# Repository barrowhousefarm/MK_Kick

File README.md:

# MK_Kick
Mortiz Klien Kick Drum

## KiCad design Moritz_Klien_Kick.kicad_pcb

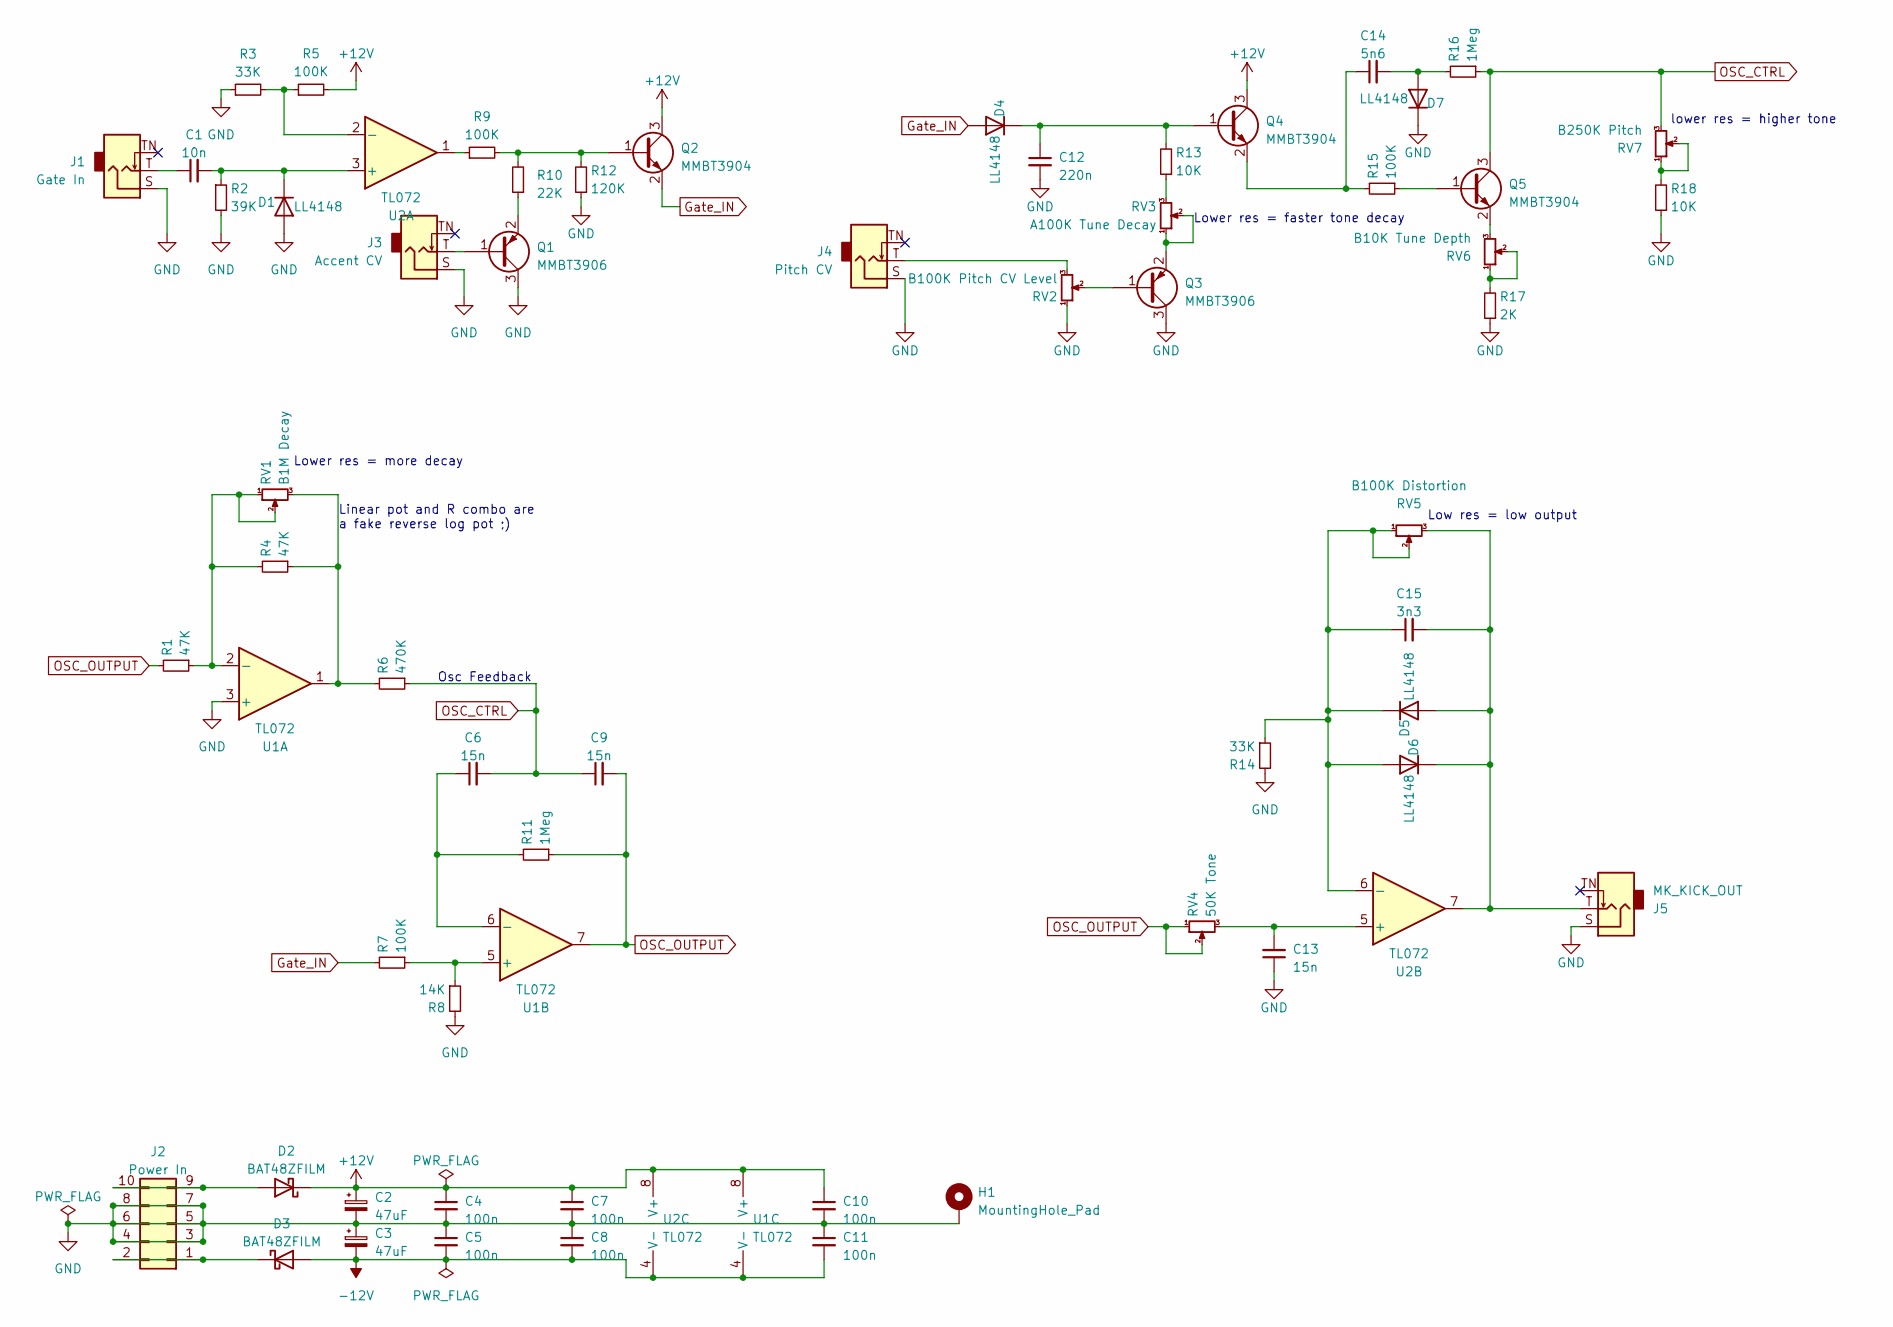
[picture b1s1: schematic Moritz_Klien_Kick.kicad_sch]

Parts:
C1: 10n; C_1210_3225Metric
C2, C3: 47uF; CP_Radial_D5.0mm_P2.50mm
C4, C5, C7, C8, C10, C11: 100n; C_1206_3216Metric
C6, C9, C13: 15n; C_1206_3216Metric
C12: 220n; C_1206_3216Metric
C14: 5n6; C_1206_3216Metric
C15: 3n3; C_1206_3216Metric
D1, D4, D5, D6, D7: LL4148; D_MiniMELF
D2, D3: BAT48ZFILM; D_MiniMELF
H1: MountingHole_Pad; MountingHole_3.2mm_M3_ISO14580_Pad
J1: Gate In; Jack_3.5mm_QingPu_WQP-PJ398SM_Vertical_CircularHoles
J2: Power In; IDC-Header_2x05_P2.54mm_Vertical
J3: Accent CV; Jack_3.5mm_QingPu_WQP-PJ398SM_Vertical_CircularHoles
J4: Pitch CV; Jack_3.5mm_QingPu_WQP-PJ398SM_Vertical_CircularHoles
J5: MK_KICK_OUT; Jack_3.5mm_QingPu_WQP-PJ398SM_Vertical_CircularHoles
Q1, Q3: MMBT3906; SOT-23
Q2, Q4, Q5: MMBT3904; SOT-23
R1, R4: 47K; R_1206_3216Metric
R2: 39K; R_1206_3216Metric
R3, R14: 33K; R_1206_3216Metric
R5, R7, R9, R15: 100K; R_1206_3216Metric
R6: 470K; R_1206_3216Metric
R8: 14K; R_1206_3216Metric
R10: 22K; R_1206_3216Metric
R11, R16: 1Meg; R_1206_3216Metric
R12: 120K; R_1206_3216Metric
R13, R18: 10K; R_1206_3216Metric
R17: 2K; R_1206_3216Metric
RV1: B1M Decay; Potentiometer_Alps_RK09K_Single_Vertical
RV2: B100K Pitch CV Level; Potentiometer_Alps_RK09K_Single_Vertical
RV3: A100K Tune Decay; Potentiometer_Alps_RK09K_Single_Vertical
RV4: 50K Tone; Potentiometer_Alps_RK09K_Single_Vertical
RV5: B100K Distortion; Potentiometer_Alps_RK09K_Single_Vertical
RV6: B10K Tune Depth; Potentiometer_Alps_RK09K_Single_Vertical
RV7: B250K Pitch; Potentiometer_Alps_RK09K_Single_Vertical
U1, U2: TL072; SO-8_5.3x6.2mm_P1.27mm

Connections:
+12V: C2.1, C4.1, C7.1, C10.1, D2.1 (K), Q2.3 (C), Q4.3 (C), R5.2, U1.8 (V+), U2.8 (V+)
-12V: C3.2, C5.2, C8.2, C11.2, D3.2 (A), U1.4 (V-), U2.4 (V-)
GND: C2.2, C3.1, C4.2, C5.1, C7.2, C8.1, C10.2, C11.1, C12.2, C13.1, D1.2 (A), D7.1 (K), H1.1, J1.S, J2.3, J2.4, J2.5, J2.6, J2.7, J2.8, J3.S, J4.S, J5.S, Q1.3 (C), Q3.3 (C), R2.2, R3.1, R8.2, R12.1, R14.2, R17.1, R18.1, RV2.1, U1.3 (+)
Gate_IN: D4.2 (A), Q2.2 (E), R7.2
unnamed: C1.1, J1.T
unnamed: C1.2, D1.1 (K), R2.1, U2.3 (+)
unnamed: D2.2 (A), J2.9, J2.10
unnamed: D3.1 (K), J2.1, J2.2
unnamed: C12.1, D4.1 (K), Q4.1 (B), R13.2
unnamed: C15.2, D5.2 (A), D6.1 (K), J5.T, RV5.3, U2.7
unnamed: C15.1, D5.1 (K), D6.2 (A), R14.1, RV5.1, RV5.2, U2.6 (-)
unnamed: C14.2, D7.2 (A), R16.2
unnamed: J4.T, RV2.3
unnamed: J3.T, Q1.1 (B)
unnamed: Q1.2 (E), R10.1
unnamed: Q2.1 (B), R9.2, R10.2, R12.2
unnamed: Q3.1 (B), RV2.2
unnamed: Q3.2 (E), RV3.1, RV3.2
unnamed: C14.1, Q4.2 (E), R15.2
unnamed: Q5.1 (B), R15.1
unnamed: Q5.2 (E), RV6.3
unnamed: R4.1, R6.2, RV1.3, U1.1
unnamed: R9.1, U2.1
unnamed: R13.1, RV3.3
unnamed: R17.2, RV6.1, RV6.2
unnamed: R18.2, RV7.1, RV7.2
unnamed: R1.1, R4.2, RV1.1, RV1.2, U1.2 (-)
unnamed: R7.1, R8.1, U1.5 (+)
unnamed: C6.1, R11.2, U1.6 (-)
unnamed: R3.2, R5.1, U2.2 (-)
unnamed: C13.2, RV4.3, U2.5 (+)
OSC_CTRL: C6.2, C9.1, Q5.3 (C), R6.1, R16.1, RV7.3
OSC_OUTPUT: C9.2, R1.2, R11.1, RV4.1, RV4.2, U1.7

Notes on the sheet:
Linear pot and R combo are a fake reverse log pot ;)
Low res = low output
Lower res = more decay
lower res = higher tone
Osc Feedback
Lower res = faster tone decay

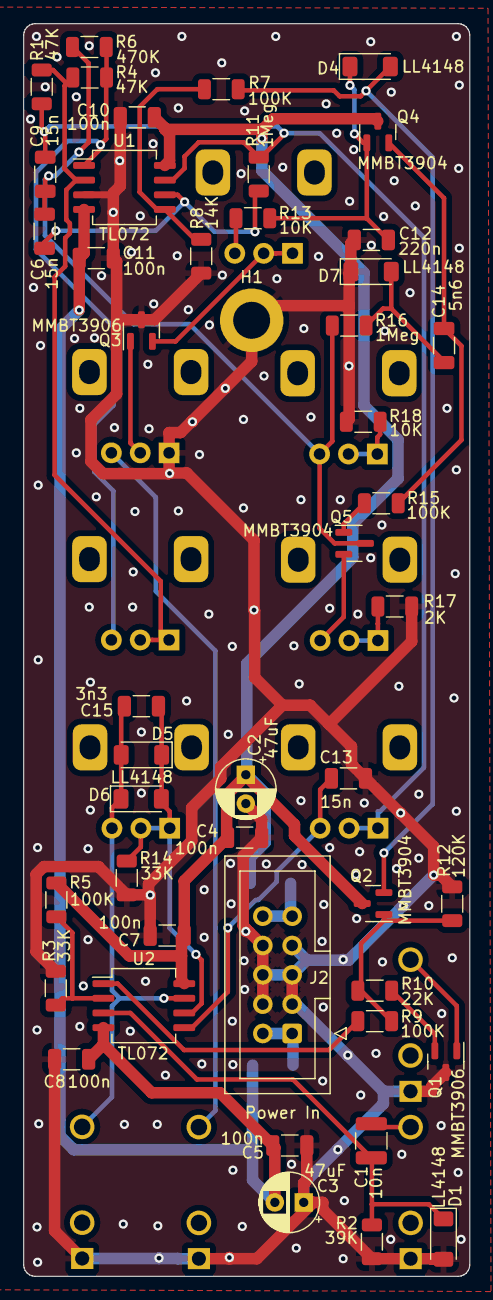
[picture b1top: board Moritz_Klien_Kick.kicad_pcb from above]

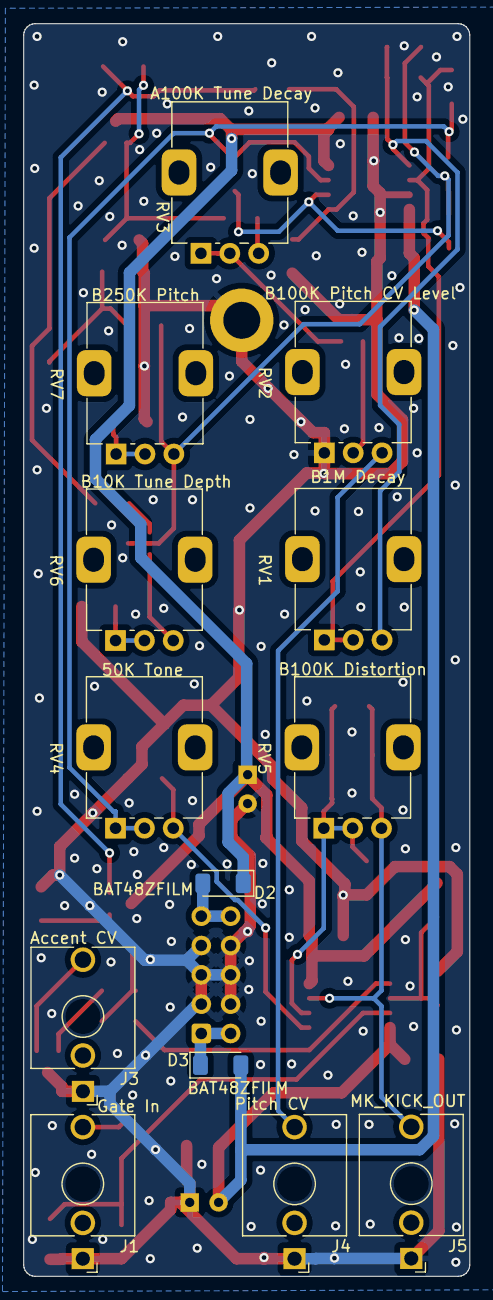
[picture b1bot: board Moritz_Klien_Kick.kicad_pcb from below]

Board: 2 copper layers, 38.6 x 108.5 mm, 60 parts (13 on the bottom side), 33 nets.

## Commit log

2024-10-25 Initial upload
2024-10-25 add kicad design files and front panel
